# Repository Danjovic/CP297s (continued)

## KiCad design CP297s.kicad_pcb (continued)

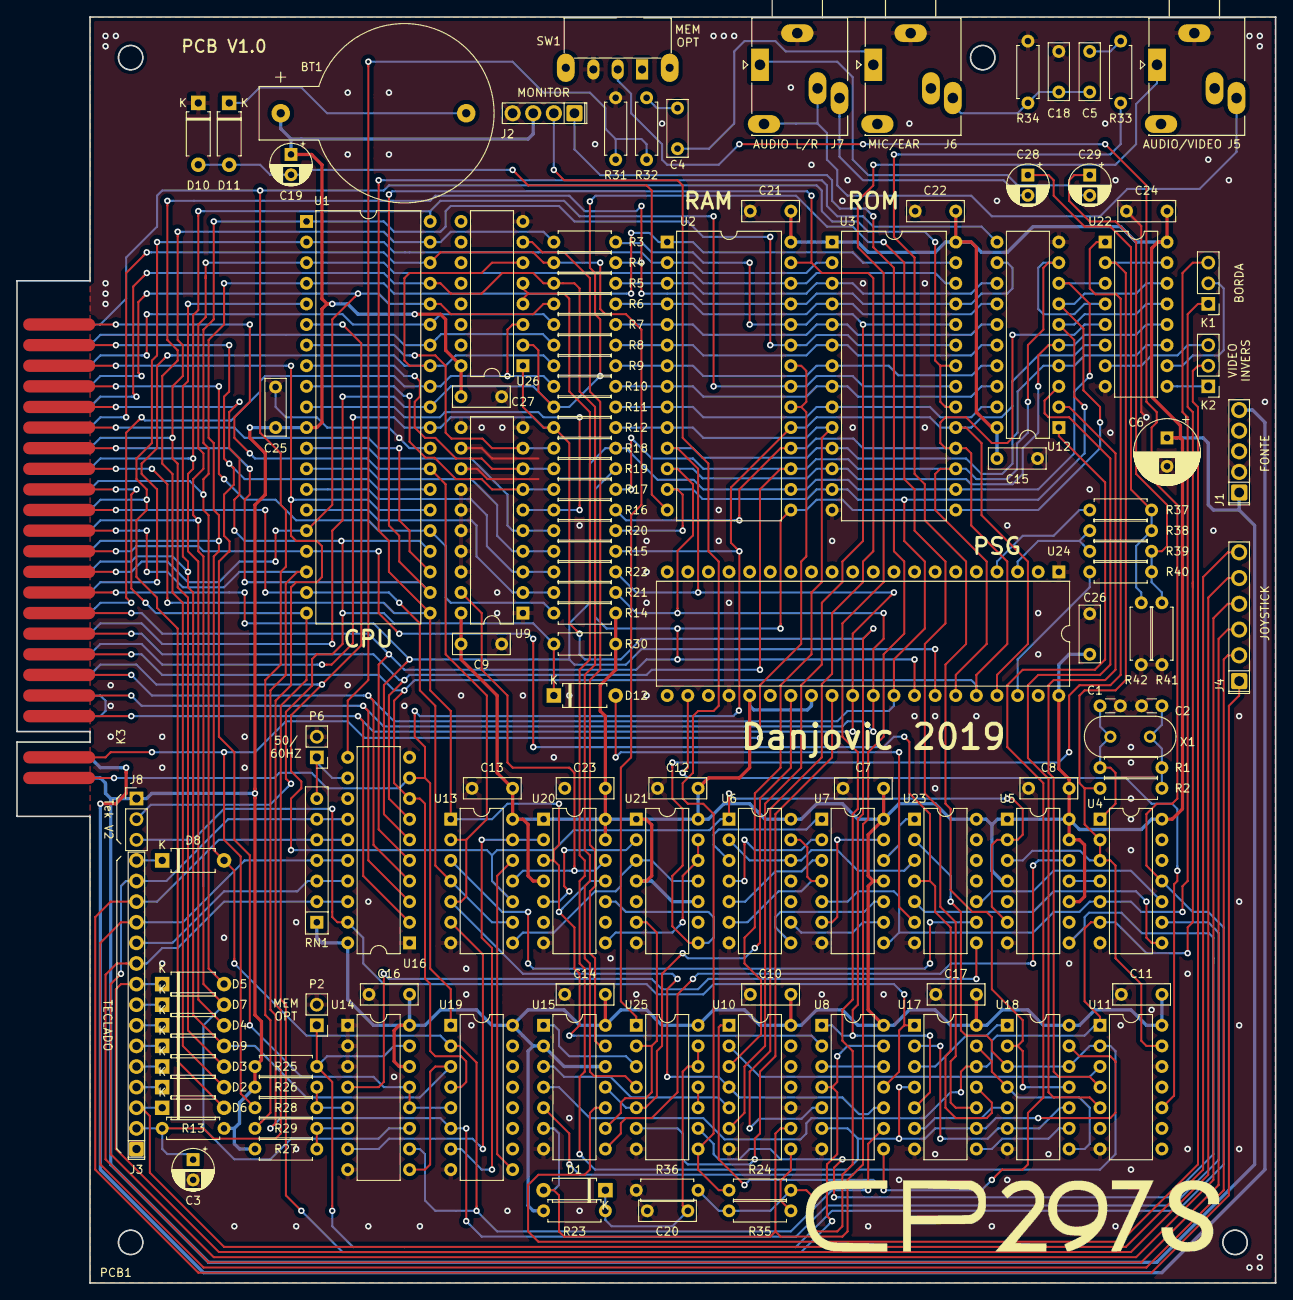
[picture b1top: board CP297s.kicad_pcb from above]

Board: 2 copper layers, 155.1 x 156.0 mm, 127 parts (0 on the bottom side), 152 nets.

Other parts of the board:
PCB1: Placa_CP200S

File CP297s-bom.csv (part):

"Source:","/home/danjovic/Área de Trabalho/ZX97 lite/CP297s/CP297s/CP297s.sch"
"Date:","Sáb 12 Out 2019 20:35:22 -03"
"Tool:","Eeschema 5.1.0-unknown-ef3f773~82~ubuntu14.04.1"
"Generator:","/usr/share/kicad/plugins/bom_csv_grouped_by_value.py"
"Component Count:","126"

"Individual Components:"

"Item","Qty","Reference(s)","Value","LibPart","Footprint","Datasheet"
"","","BT1","Battery_Cell","Device:Battery_Cell","Battery:BatteryHolder_CR2032H","~"
"","","C1","22p","CP297s:C-CP297s","Capacitor_THT:C_Disc_D3.0mm_W1.6mm_P2.50mm",""
"","","C2","22p","CP297s:C-CP297s","Capacitor_THT:C_Disc_D3.0mm_W1.6mm_P2.50mm",""
"","","C3","1uF","CP297s:CAPAPOL-CP297s","Capacitor_THT:CP_Radial_D5.0mm_P2.50mm","~"
"","","C4","47n","CP297s:C-CP297s","Capacitor_THT:C_Disc_D7.0mm_W2.5mm_P5.00mm","~"
"","","C5","100n","CP297s:C-CP297s","Capacitor_THT:C_Disc_D7.0mm_W2.5mm_P5.00mm","~"
"","","C6","100u","CP297s:CAPAPOL-CP297s","Capacitor_THT:CP_Radial_D8.0mm_P3.50mm","~"
"","","C7","100n","CP297s:C-CP297s","Capacitor_THT:C_Disc_D7.0mm_W2.5mm_P5.00mm","~"
"","","C8","100n","CP297s:C-CP297s","Capacitor_THT:C_Disc_D7.0mm_W2.5mm_P5.00mm","~"
"","","C9","100n","CP297s:C-CP297s","Capacitor_THT:C_Disc_D7.0mm_W2.5mm_P5.00mm","~"
"","","C10","100n","CP297s:C-CP297s","Capacitor_THT:C_Disc_D7.0mm_W2.5mm_P5.00mm","~"
"","","C11","100n","CP297s:C-CP297s","Capacitor_THT:C_Disc_D7.0mm_W2.5mm_P5.00mm","~"
"","","C12","100n","CP297s:C-CP297s","Capacitor_THT:C_Disc_D7.0mm_W2.5mm_P5.00mm","~"
"","","C13","100n","CP297s:C-CP297s","Capacitor_THT:C_Disc_D7.0mm_W2.5mm_P5.00mm","~"
"","","C14","100n","CP297s:C-CP297s","Capacitor_THT:C_Disc_D7.0mm_W2.5mm_P5.00mm","~"
"","","C15","100n","CP297s:C-CP297s","Capacitor_THT:C_Disc_D7.0mm_W2.5mm_P5.00mm","~"
"","","C16","100n","CP297s:C-CP297s","Capacitor_THT:C_Disc_D7.0mm_W2.5mm_P5.00mm","~"
"","","C17","100n","CP297s:C-CP297s","Capacitor_THT:C_Disc_D7.0mm_W2.5mm_P5.00mm","~"
"","","C18","47n","CP297s:C-CP297s","Capacitor_THT:C_Disc_D7.0mm_W2.5mm_P5.00mm","~"
"","","C19","1uF","CP297s:CAPAPOL-CP297s","Capacitor_THT:CP_Radial_D5.0mm_P2.50mm","~"
"","","C20","10n","CP297s:C-CP297s","Capacitor_THT:C_Disc_D7.0mm_W2.5mm_P5.00mm","~"
"","","C21","100n","CP297s:C-CP297s","Capacitor_THT:C_Disc_D7.0mm_W2.5mm_P5.00mm","~"
"","","C22","100n","CP297s:C-CP297s","Capacitor_THT:C_Disc_D7.0mm_W2.5mm_P5.00mm","~"
"","","C23","100n","CP297s:C-CP297s","Capacitor_THT:C_Disc_D7.0mm_W2.5mm_P5.00mm","~"
"","","C24","100n","CP297s:C-CP297s","Capacitor_THT:C_Disc_D7.0mm_W2.5mm_P5.00mm","~"
"","","C25","100n","CP297s:C-CP297s","Capacitor_THT:C_Disc_D7.0mm_W2.5mm_P5.00mm","~"
"","","C26","100n","CP297s:C-CP297s","Capacitor_THT:C_Disc_D7.0mm_W2.5mm_P5.00mm","~"
"","","C27","100n","CP297s:C-CP297s","Capacitor_THT:C_Disc_D7.0mm_W2.5mm_P5.00mm","~"
"","","C28","1uF","CP297s:CAPAPOL-CP297s","Capacitor_THT:CP_Radial_D5.0mm_P2.50mm","~"
"","","C29","1uF","CP297s:CAPAPOL-CP297s","Capacitor_THT:CP_Radial_D5.0mm_P2.50mm","~"
"","","D1","4148","CP297s:DIODE-CP297s","Diode_THT:D_A-405_P7.62mm_Horizontal",""
"","","D2","4148","CP297s:DIODE-CP297s","Diode_THT:D_A-405_P7.62mm_Horizontal","~"
"","","D3","4148","CP297s:DIODE-CP297s","Diode_THT:D_A-405_P7.62mm_Horizontal","~"
"","","D4","4148","CP297s:DIODE-CP297s","Diode_THT:D_A-405_P7.62mm_Horizontal","~"
"","","D5","4148","CP297s:DIODE-CP297s","Diode_THT:D_A-405_P7.62mm_Horizontal","~"
"","","D6","4148","CP297s:DIODE-CP297s","Diode_THT:D_A-405_P7.62mm_Horizontal","~"
"","","D7","4148","CP297s:DIODE-CP297s","Diode_THT:D_A-405_P7.62mm_Horizontal","~"
"","","D8","4148","CP297s:DIODE-CP297s","Diode_THT:D_A-405_P7.62mm_Horizontal","~"
"","","D9","4148","CP297s:DIODE-CP297s","Diode_THT:D_A-405_P7.62mm_Horizontal","~"
"","","D10","BAT41","Diode:BAT41","Diode_THT:D_A-405_P7.62mm_Horizontal","http://www.vishay.com/docs/85659/bat41.pdf"
"","","D11","BAT41","Diode:BAT41","Diode_THT:D_A-405_P7.62mm_Horizontal","http://www.vishay.com/docs/85659/bat41.pdf"
"","","D12","4148","CP297s:DIODE-CP297s","Diode_THT:D_A-405_P7.62mm_Horizontal",""
"","","J1","Conn_01x05_Male","CP297s:Conn_01x05_Male-Connector","CP297s:CP200S_FONTE","~"
"","","J2","Conn_01x04_Female","CP297s:Conn_01x04_Female-Connector","CP297s:CP200S_VIDEO","~"
"","","J3","pin header 01x15 2.54mm","CP297s:Conn_01x15_Male-Connector","CP297s:CP200s_Keyboard","~"
"","","J4","Conn_01x06_Female","CP297s:Conn_01x06_Female-Connector","CP297s:CP200S_JOYSTICK","~"
"","","J5","PG203J","Connector_Specialized:Audio-Jack-3_2Switches","CP297s:PG203J","~"
"","","J6","PG203J","Connector_Specialized:Audio-Jack-3_2Switches","CP297s:PG203J","~"
"","","J7","PG203J","Connector_Specialized:Audio-Jack-3_2Switches","CP297s:PG203J","~"
"","","J8","Conn_01x03_Female","Connector_Generic:Conn_01x03_Female","Connector_PinHeader_2.54mm:PinHeader_1x03_P2.54mm_Vertical","~"
"","","K1","CONN_3","CP297s:CONN_3-CP297s","Connector_PinHeader_2.54mm:PinHeader_1x03_P2.54mm_Vertical",""
"","","K2","CONN_3","CP297s:CONN_3-CP297s","Connector_PinHeader_2.54mm:PinHeader_1x03_P2.54mm_Vertical",""
"","","K3","TK85_BUS","CP297s:TK85_BUS-CP297s","CP297s:ZX81_EDGE",""
"","","P2","CONN_2","CP297s:CONN_2-CP297s","Connector_PinHeader_2.54mm:PinHeader_1x02_P2.54mm_Vertical",""
"","","P6","CONN_2","CP297s:CONN_2-CP297s","Connector_PinHeader_2.54mm:PinHeader_1x02_P2.54mm_Vertical",""
"","","R1","20M","CP297s:R-CP297s","Resistor_THT:R_Axial_DIN0207_L6.3mm_D2.5mm_P7.62mm_Horizontal",""
"","","R2","2k","CP297s:R-CP297s","Resistor_THT:R_Axial_DIN0207_L6.3mm_D2.5mm_P7.62mm_Horizontal",""
"","","R3","1k","CP297s:R-CP297s","Resistor_THT:R_Axial_DIN0207_L6.3mm_D2.5mm_P7.62mm_Horizontal","~"
"","","R4","1k","CP297s:R-CP297s","Resistor_THT:R_Axial_DIN0207_L6.3mm_D2.5mm_P7.62mm_Horizontal","~"
"","","R5","1k","CP297s:R-CP297s","Resistor_THT:R_Axial_DIN0207_L6.3mm_D2.5mm_P7.62mm_Horizontal","~"
"","","R6","1k","CP297s:R-CP297s","Resistor_THT:R_Axial_DIN0207_L6.3mm_D2.5mm_P7.62mm_Horizontal","~"
"","","R7","1k","CP297s:R-CP297s","Resistor_THT:R_Axial_DIN0207_L6.3mm_D2.5mm_P7.62mm_Horizontal","~"
"","","R8","1k","CP297s:R-CP297s","Resistor_THT:R_Axial_DIN0207_L6.3mm_D2.5mm_P7.62mm_Horizontal","~"
"","","R9","1k","CP297s:R-CP297s","Resistor_THT:R_Axial_DIN0207_L6.3mm_D2.5mm_P7.62mm_Horizontal","~"
"","","R10","1k","CP297s:R-CP297s","Resistor_THT:R_Axial_DIN0207_L6.3mm_D2.5mm_P7.62mm_Horizontal","~"
"","","R11","1k","CP297s:R-CP297s","Resistor_THT:R_Axial_DIN0207_L6.3mm_D2.5mm_P7.62mm_Horizontal","~"
"","","R12","1k","CP297s:R-CP297s","Resistor_THT:R_Axial_DIN0207_L6.3mm_D2.5mm_P7.62mm_Horizontal","~"
"","","R13","10K","CP297s:R-CP297s","Resistor_THT:R_Axial_DIN0207_L6.3mm_D2.5mm_P7.62mm_Horizontal","~"
"","","R14","10K","CP297s:R-CP297s","Resistor_THT:R_Axial_DIN0207_L6.3mm_D2.5mm_P7.62mm_Horizontal","~"
"","","R15","1k","CP297s:R-CP297s","Resistor_THT:R_Axial_DIN0207_L6.3mm_D2.5mm_P7.62mm_Horizontal","~"
"","","R16","1k","CP297s:R-CP297s","Resistor_THT:R_Axial_DIN0207_L6.3mm_D2.5mm_P7.62mm_Horizontal","~"
"","","R17","1k","CP297s:R-CP297s","Resistor_THT:R_Axial_DIN0207_L6.3mm_D2.5mm_P7.62mm_Horizontal","~"
"","","R18","1k","CP297s:R-CP297s","Resistor_THT:R_Axial_DIN0207_L6.3mm_D2.5mm_P7.62mm_Horizontal","~"
"","","R19","1k","CP297s:R-CP297s","Resistor_THT:R_Axial_DIN0207_L6.3mm_D2.5mm_P7.62mm_Horizontal","~"
"","","R20","1k","CP297s:R-CP297s","Resistor_THT:R_Axial_DIN0207_L6.3mm_D2.5mm_P7.62mm_Horizontal","~"
"","","R21","1k","CP297s:R-CP297s","Resistor_THT:R_Axial_DIN0207_L6.3mm_D2.5mm_P7.62mm_Horizontal","~"
"","","R22","1k","CP297s:R-CP297s","Resistor_THT:R_Axial_DIN0207_L6.3mm_D2.5mm_P7.62mm_Horizontal","~"
"","","R23","1k2","CP297s:R-CP297s","Resistor_THT:R_Axial_DIN0207_L6.3mm_D2.5mm_P7.62mm_Horizontal",""
"","","R24","220","CP297s:R-CP297s","Resistor_THT:R_Axial_DIN0207_L6.3mm_D2.5mm_P7.62mm_Horizontal",""
"","","R25","10K","CP297s:R-CP297s","Resistor_THT:R_Axial_DIN0207_L6.3mm_D2.5mm_P7.62mm_Horizontal","~"
"","","R26","2K2","CP297s:R-CP297s","Resistor_THT:R_Axial_DIN0207_L6.3mm_D2.5mm_P7.62mm_Horizontal","~"
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
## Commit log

2019-07-02 upload files
2019-07-02 remove backup file
2019-07-03 updated pcb layout, added logo
2019-07-04 added psgs in symbols library
2019-07-08 add PSG, changed AV connectors
2019-07-13 moved battery clip, substituted audio-mono for +5Vcc at MONITOR OUT connector
2019-07-23 updated board outline, support for external kolour
2019-08-07 Added resistor network at keyboard inputs
2019-08-07 added revision version in top silk
2019-08-08 fixed CPU syncrhonizer (/wait logic)
2019-08-11 Added header for Tek V2
2019-08-31 Aesthetic improvement, gerbers added
2019-08-31 cleanup
2019-10-12 added schematic in PDF and BOM in csv
2019-10-22 Added components map on the board
